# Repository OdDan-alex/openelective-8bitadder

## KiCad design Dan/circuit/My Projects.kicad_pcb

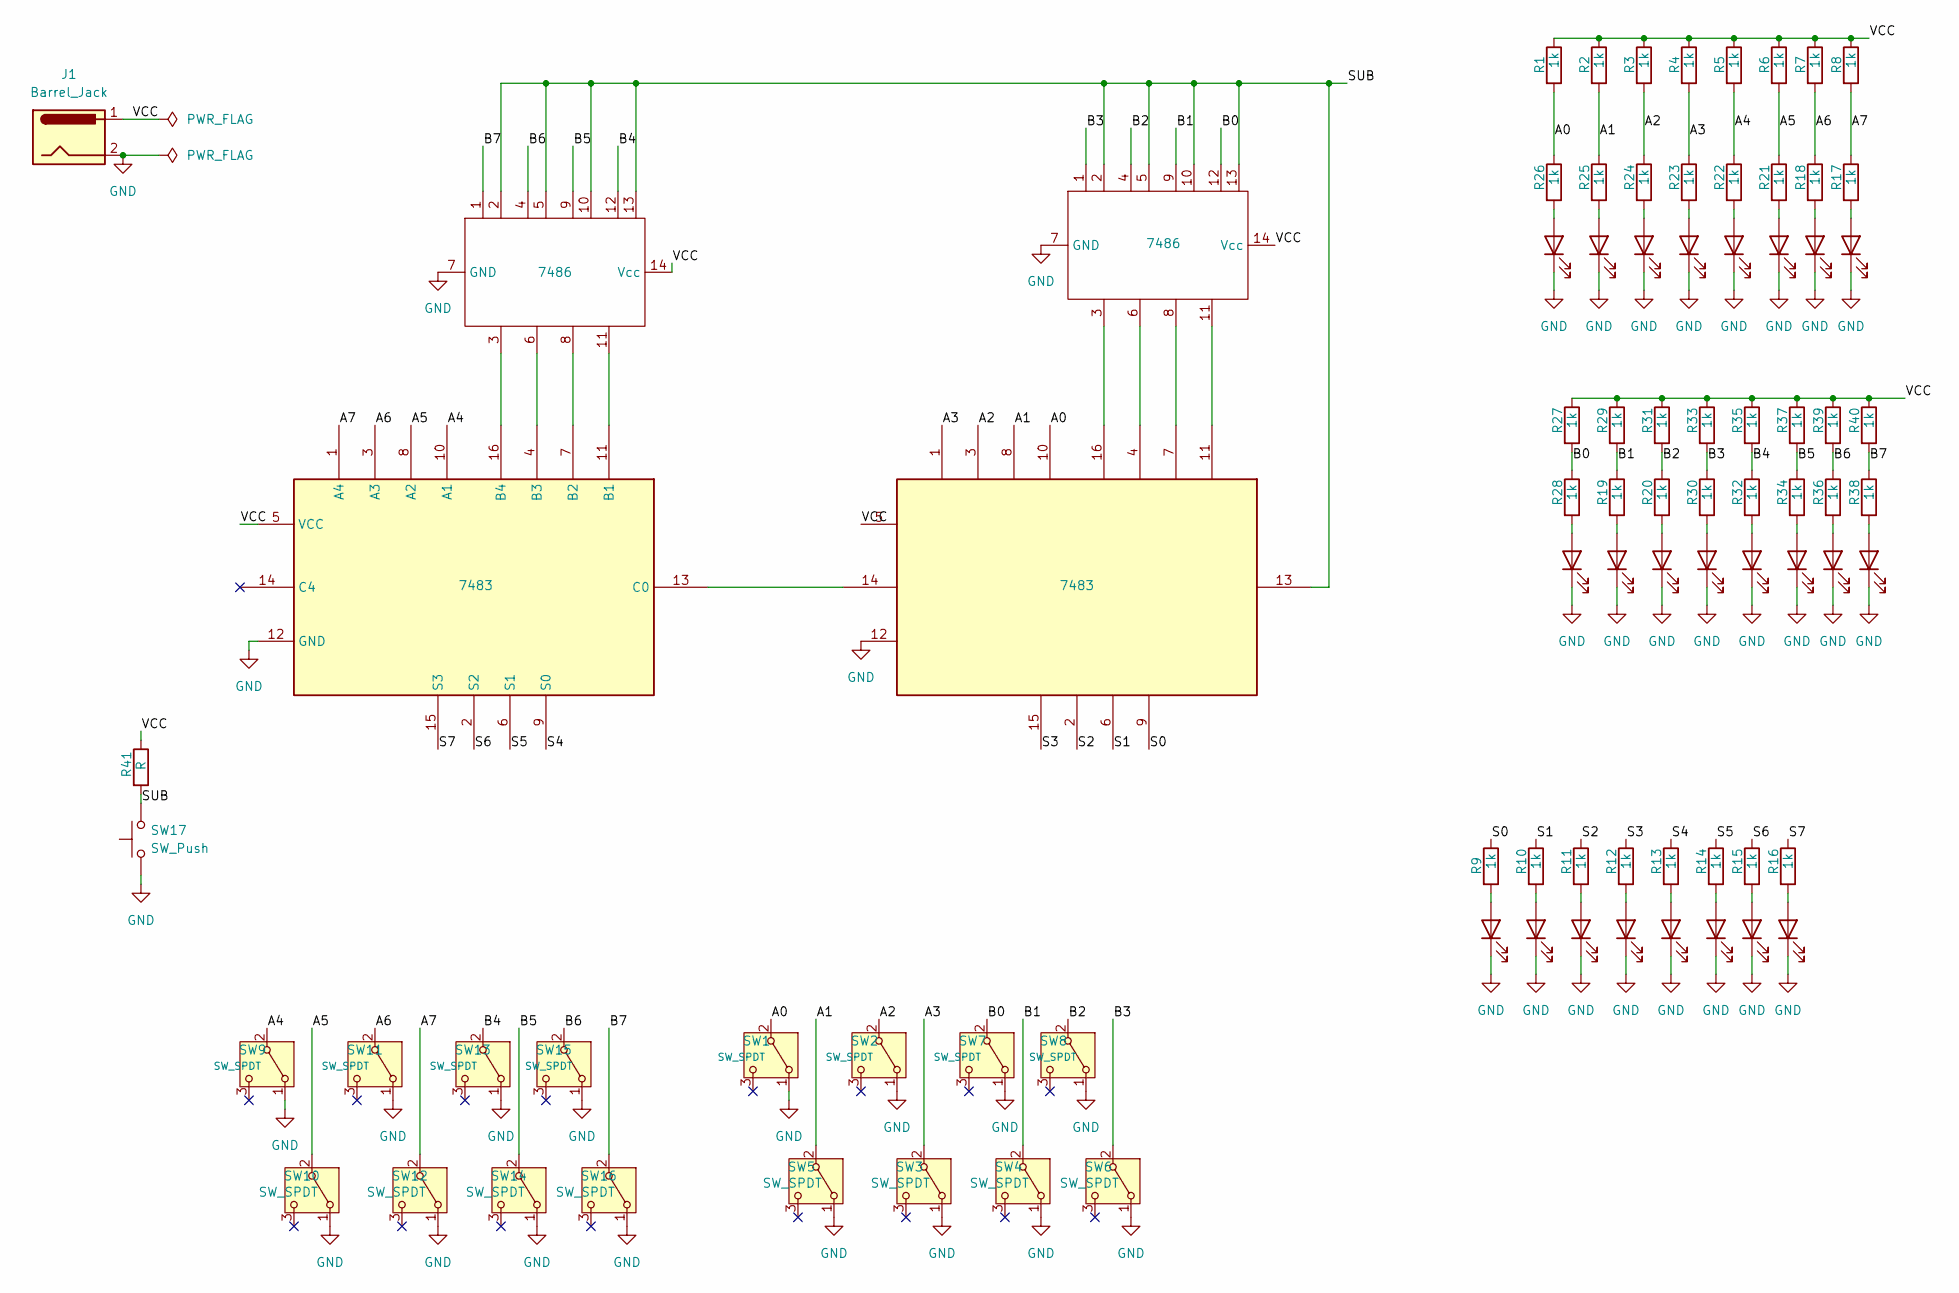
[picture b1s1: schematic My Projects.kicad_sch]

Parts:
D1, D2, D3, D4, D5, D6, D7, D8, D9, D10, D11, D12, D13, D14, D15, D16, D18, D19, D20, D21, D22, D23, D24, D25: LED; LED_D3.0mm
IC1, IC2: 7483; DIP-16_W7.62mm
IC3, IC4: 7486; DIP-14_W7.62mm
J1: Barrel_Jack; BarrelJack_GCT_DCJ200-10-A_Horizontal
R1, R2, R3, R4, R5, R6, R7, R8, R9, R10, R11, R12, R13, R14, R15, R16, R17, R18, R19, R20, R21, R22, R23, R24, R25, R26, R27, R28, R29, R30, R31, R32, R33, R34, R35, R36, R37, R38, R39, R40: 1k; R_Axial_DIN0204_L3.6mm_D1.6mm_P5.08mm_Horizontal
R41: R; R_Axial_DIN0204_L3.6mm_D1.6mm_P5.08mm_Horizontal
SW1, SW2, SW3, SW4, SW5, SW6, SW7, SW8, SW9, SW10, SW11, SW12, SW13, SW14, SW15, SW16: SW_SPDT; LED SWITCH3pin
SW17: SW_Push; SW_PUSH_6mm

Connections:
/A0: IC2.10 (A1), R1.2, R26.1, SW1.2 (B)
/A1: IC2.8 (A2), R2.2, R25.1, SW5.2 (B)
/A2: IC2.3 (A3), R3.2, R24.1, SW2.2 (B)
/A3: IC2.1 (A4), R4.2, R23.1, SW3.2 (B)
/A4: IC1.10 (A1), R5.2, R22.1, SW9.2 (B)
/A5: IC1.8 (A2), R6.2, R21.1, SW10.2 (B)
/A6: IC1.3 (A3), R7.2, R18.1, SW11.2 (B)
/A7: IC1.1 (A4), R8.2, R17.1, SW12.2 (B)
/B0: IC4.12, R27.2, R28.1, SW7.2 (B)
/B1: IC4.9, R19.1, R29.2, SW4.2 (B)
/B2: IC4.4, R20.1, R31.2, SW8.2 (B)
/B3: IC4.1, R30.1, R33.2, SW6.2 (B)
/B4: IC3.12, R32.1, R35.2, SW13.2 (B)
/B5: IC3.9, R34.1, R37.2, SW14.2 (B)
/B6: IC3.4, R36.1, R39.2, SW15.2 (B)
/B7: IC3.1, R38.1, R40.2, SW16.2 (B)
/S0: IC2.9 (S0), R9.1
/S1: IC2.6 (S1), R10.1
/S2: IC2.2 (S2), R11.1
/S3: IC2.15 (S3), R12.1
/S4: IC1.9 (S0), R13.1
/S5: IC1.6 (S1), R14.1
/S6: IC1.2 (S2), R15.1
/S7: IC1.15 (S3), R16.1
/SUB: IC2.13 (C0), IC3.2, IC3.5, IC3.10, IC3.13, IC4.2, IC4.5, IC4.10, IC4.13, R41.2, SW17.2
/VCC: IC1.5 (VCC), IC2.5 (VCC), IC3.14 (Vcc), IC4.14 (Vcc), J1.1, R1.1, R2.1, R3.1, R4.1, R5.1, R6.1, R7.1, R8.1, R27.1, R29.1, R31.1, R33.1, R35.1, R37.1, R39.1, R40.1, R41.1
GND: D1.1 (K), D2.1 (K), D3.1 (K), D4.1 (K), D5.1 (K), D6.1 (K), D7.1 (K), D8.1 (K), D9.1 (K), D10.1 (K), D11.1 (K), D12.1 (K), D13.1 (K), D14.1 (K), D15.1 (K), D16.1 (K), D18.1 (K), D19.1 (K), D20.1 (K), D21.1 (K), D22.1 (K), D23.1 (K), D24.1 (K), D25.1 (K), IC1.12 (GND), IC2.12 (GND), IC3.7 (GND), IC4.7 (GND), J1.2, SW1.1 (A), SW2.1 (A), SW3.1 (A), SW4.1 (A), SW5.1 (A), SW6.1 (A), SW7.1 (A), SW8.1 (A), SW9.1 (A), SW10.1 (A), SW11.1 (A), SW12.1 (A), SW13.1 (A), SW14.1 (A), SW15.1 (A), SW16.1 (A), SW17.1
unnamed: D1.2 (A), R26.2
unnamed: D2.2 (A), R25.2
unnamed: D3.2 (A), R24.2
unnamed: D4.2 (A), R23.2
unnamed: D5.2 (A), R22.2
unnamed: D6.2 (A), R21.2
unnamed: D7.2 (A), R18.2
unnamed: D8.2 (A), R17.2
unnamed: D9.2 (A), R9.2
unnamed: D10.2 (A), R10.2
unnamed: D11.2 (A), R11.2
unnamed: D12.2 (A), R12.2
unnamed: D13.2 (A), R13.2
unnamed: D14.2 (A), R14.2
unnamed: D15.2 (A), R15.2
unnamed: D16.2 (A), R16.2
unnamed: D18.2 (A), R28.2
unnamed: D19.2 (A), R19.2
unnamed: D20.2 (A), R20.2
unnamed: D21.2 (A), R30.2
unnamed: D22.2 (A), R32.2
unnamed: D23.2 (A), R34.2
unnamed: D24.2 (A), R36.2
unnamed: D25.2 (A), R38.2
unnamed: IC1.11 (B1), IC3.11
unnamed: IC1.7 (B2), IC3.8
unnamed: IC1.4 (B3), IC3.6
unnamed: IC1.16 (B4), IC3.3
unnamed: IC1.13 (C0), IC2.14 (C4)
unnamed: IC2.11 (B1), IC4.11
unnamed: IC2.7 (B2), IC4.8
unnamed: IC2.4 (B3), IC4.6
unnamed: IC2.16 (B4), IC4.3

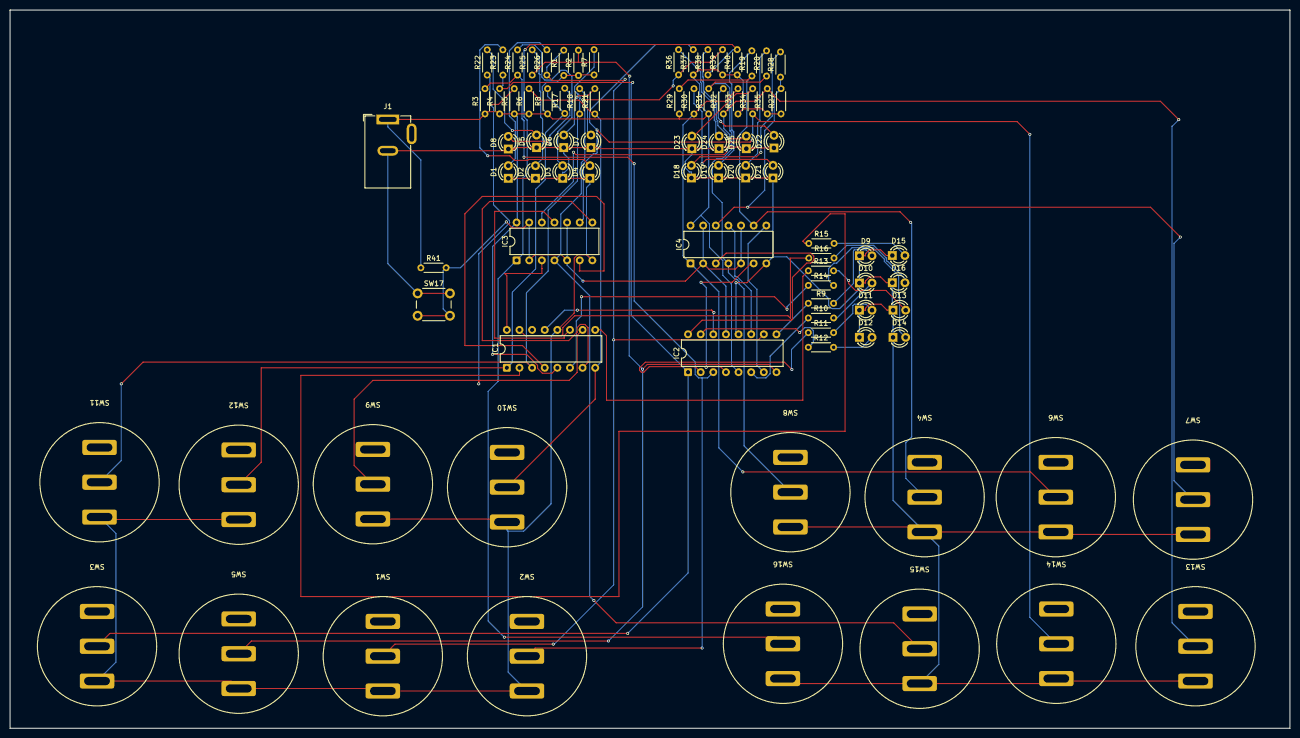
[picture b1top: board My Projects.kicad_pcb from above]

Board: 2 copper layers, 257.5 x 144.5 mm, 87 parts (0 on the bottom side), 60 nets.
